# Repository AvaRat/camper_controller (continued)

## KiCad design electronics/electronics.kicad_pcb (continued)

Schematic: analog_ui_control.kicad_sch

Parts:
C16, C26: C_Polarized; CP_Radial_D5.0mm_P2.50mm
C25: 10uF; C_0805_2012Metric
C27: 100nF; C_0805_2012Metric
J3: Conn_01x08; TerminalBlock_Xinya_XY308-2.54-8P_1x08_P2.54mm_Horizontal

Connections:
+5V: C16.1, C25.2, C26.1, C27.2, J3.1; also elsewhere on the board
/central_control_unit/analog_ui_rmt_led: J3.3; also elsewhere on the board
/central_control_unit/btn_1: J3.4; also elsewhere on the board
/central_control_unit/btn_2: J3.5; also elsewhere on the board
/central_control_unit/btn_3: J3.6; also elsewhere on the board
/central_control_unit/btn_4: J3.7; also elsewhere on the board
/central_control_unit/btn_5: J3.8; also elsewhere on the board
GND_LP: C16.2, C25.1, C26.2, C27.1, J3.2; also elsewhere on the board

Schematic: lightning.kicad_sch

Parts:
C1, C3: C_Polarized; CP_Radial_D5.0mm_P2.50mm; not fitted
C2, C4: C; C_0805_2012Metric; not fitted
F6: 5A; ATO_fuse_holder; LCSC_part C2935871
J1: leds_ch1; TerminalBlock_Xinya_XY308-2.54-3P_1x03_P2.54mm_Horizontal
J20: leds_ch2; TerminalBlock_Xinya_XY308-2.54-3P_1x03_P2.54mm_Horizontal
J26: leds_ch3; TerminalBlock_Xinya_XY308-2.54-3P_1x03_P2.54mm_Horizontal
J27: leds_ch4; TerminalBlock_Xinya_XY308-2.54-3P_1x03_P2.54mm_Horizontal
Q6: Q_NMOS_GDS; SOT-23; Mrf_part AO3400-HXY; JLC C4748804
R1: 47k; R_0805_2012Metric
R2: 470R; R_0805_2012Metric
U2: ISO6740; SOIC-16W_7.5x10.3mm_P1.27mm; not fitted
U4: generic_dcdc; not fitted

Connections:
+5V_LEDs: C3.1, C4.1, J1.3, J20.3, J26.3, J27.3, U4.3 (VOUT)
+12V_HP: F6.1; also elsewhere on the board
/central_control_unit/LED_CH1: J1.2, U2.3 (INA), U2.14 (OUTA); also elsewhere on the board
/central_control_unit/LED_CH2: J20.2, U2.4 (INB), U2.13 (OUTB); also elsewhere on the board
/central_control_unit/LED_CH3: J26.2, U2.5 (INC), U2.12 (OUTC); also elsewhere on the board
/central_control_unit/LED_CH4: J27.2, U2.6 (IND), U2.11 (OUTD); also elsewhere on the board
/central_control_unit/led_en: R2.1; also elsewhere on the board
GND_HP: C1.2, C2.2, Q6.3 (S), R1.2, U2.9 (GND2), U2.15 (GND2); also elsewhere on the board
GND_LEDs: C3.2, C4.2, J1.1, J20.1, J26.1, J27.1, U4.4 (GND)
unnamed: Q6.2 (D), U4.2 (GND)
unnamed: Q6.1 (G), R1.1, R2.2
unnamed: U2.2 (GND1), U2.8 (GND1)
unnamed: C1.1, C2.1, F6.2, U4.1 (VIN)

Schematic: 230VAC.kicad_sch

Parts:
C9: 4.7uF; C_0805_2012Metric
C34: C; C_Disc_D3.0mm_W2.0mm_P2.50mm
D2: 1N4148W; D_SOD-123; MFG part nr 1N4148W; lcsc C917030
J21, J22: Conn_01x02; TerminalBlock_Xinya_XY308-2.54-2P_1x02_P2.54mm_Horizontal
Q5: Q_NMOS_GDS; SOT-23; Mrf_part AO3400-HXY; JLC C4748804
R22: 470R; R_0805_2012Metric
R23, R24: 100k; R_Axial_DIN0207_L6.3mm_D2.5mm_P7.62mm_Horizontal
R25: 4.7kΩ; R_0805_2012Metric
R41: 47k; R_0805_2012Metric
RL1: AZSR131-1AE-12D; PRE29-same-sky; MFG Part Nr PRE29-5V-S-450; not fitted
U17: LTV-814; DIP-4_W7.62mm; mouser 859-LTV-814S-TA1-A

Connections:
+3.3V: R25.1; also elsewhere on the board
+5V: D2.1 (K), RL1.2; also elsewhere on the board
/central_control_unit/230VAC/N_230VAC: J21.2, R24.1
/central_control_unit/230VAC/P_230VAC: J21.1, R23.1
/central_control_unit/ac_detect: C9.1, R25.2, U17.4; also elsewhere on the board
/central_control_unit/relay_out: R22.1; also elsewhere on the board
GND_LP: C9.2, Q5.3 (S), R41.2, U17.3; also elsewhere on the board
unnamed: C34.1, R23.2, U17.1
unnamed: C34.2, R24.2, U17.2
unnamed: D2.2 (A), Q5.2 (D), RL1.1
unnamed: J22.1, RL1.4
unnamed: J22.2, RL1.3
unnamed: Q5.1 (G), R22.2, R41.1

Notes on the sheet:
230VAC Detection
25mA LED current

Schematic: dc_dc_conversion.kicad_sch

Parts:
D1, D13, D14: LED; LED_1206_3216Metric
D15: D_Schottky; D_SMA
FB1: FerriteBead 47 Ohm; L_Walsin_WLFM201609x
J25: header; PinHeader_1x02_P2.54mm_Vertical
Q1: Q_NMOS_DGS; SOT-323_SC-70
Q2: Q_PMOS_DGS; SOT-323_SC-70
R3, R4, R18, R33, R34, R35: 4k7; R_0805_2012Metric
R36: 470R; R_0805_2012Metric
R37, R38: 47k; R_0805_2012Metric
U1: TLV1117-33; SOT-223-3_TabPin2; JLC C37359
U18: mini360; not fitted

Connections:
+3.3V: R4.2, U1.2 (VO); also elsewhere on the board
+5V: J25.2, R18.2, U1.3 (VI), U18.3 (VOUT); also elsewhere on the board
+12V: Q2.3 (S), R33.2, R38.1, U18.1 (VIN); also elsewhere on the board
/central_control_unit/USB_VIN: D15.2 (A), R36.2; also elsewhere on the board
/central_control_unit/dc_dc_conversion/USB_VBUS: D15.1 (K), J25.1
/central_control_unit/dc_dc_conversion/vin: Q2.1 (D)
GND_HP: FB1.2, U18.2 (GND), U18.4 (GND); also elsewhere on the board
GND_LP: D1.1 (K), D13.1 (K), D14.1 (K), FB1.1, Q1.3 (S), R37.2, U1.1 (GND); also elsewhere on the board
unnamed: D1.2 (A), R35.1
unnamed: D13.2 (A), R4.1
unnamed: D14.2 (A), R3.1
unnamed: Q1.1 (D), Q2.2 (G), R38.2
unnamed: Q1.2 (G), R36.1, R37.1
unnamed: R3.2, R18.1
unnamed: R33.1, R34.1
unnamed: R34.2, R35.2

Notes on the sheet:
USB_VSYS disconnets 12V to 5V DC/DC converter
Green LEDs
5V 6A max

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
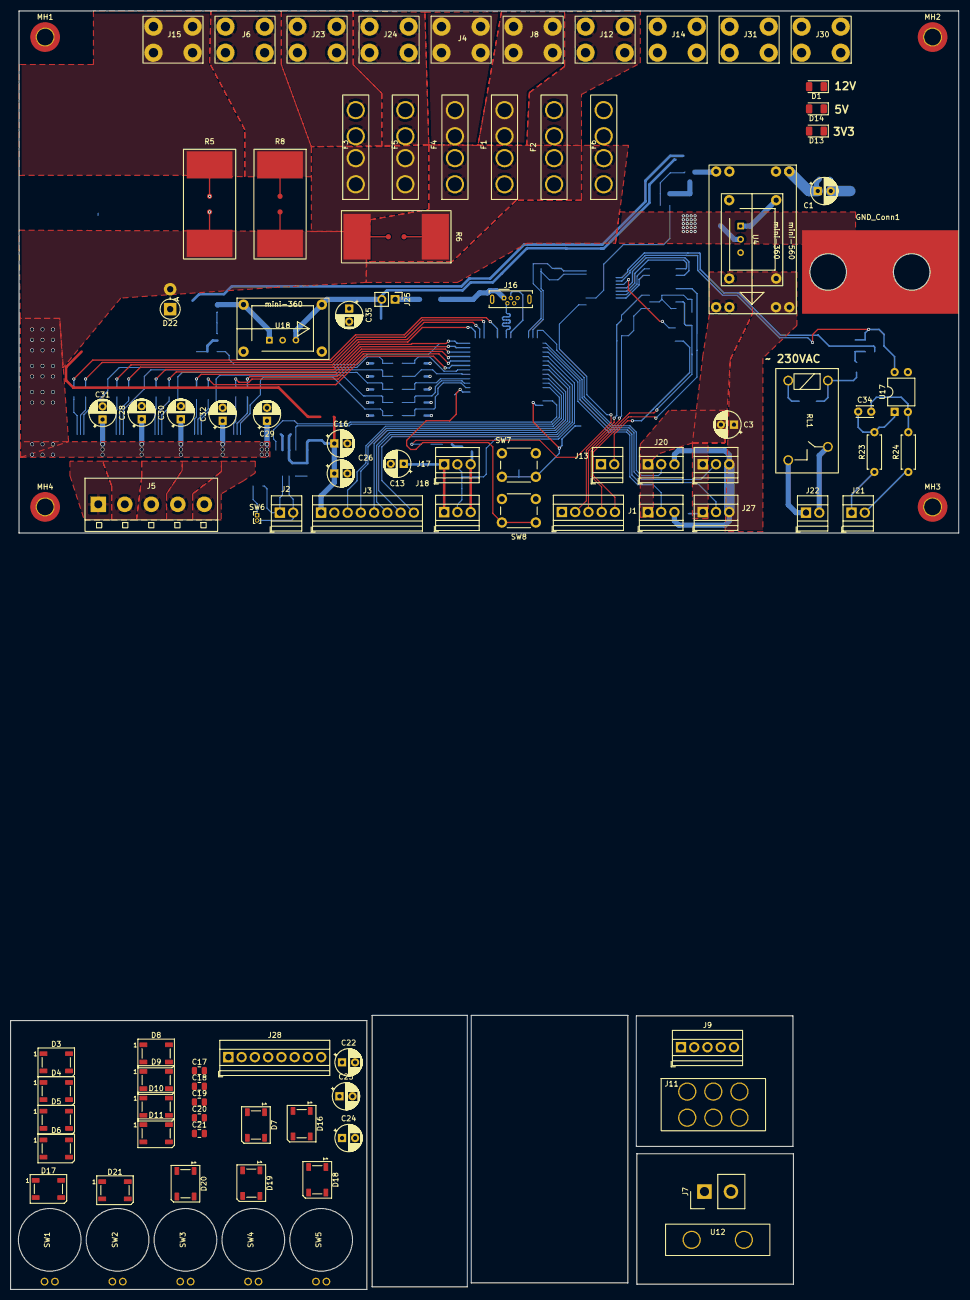
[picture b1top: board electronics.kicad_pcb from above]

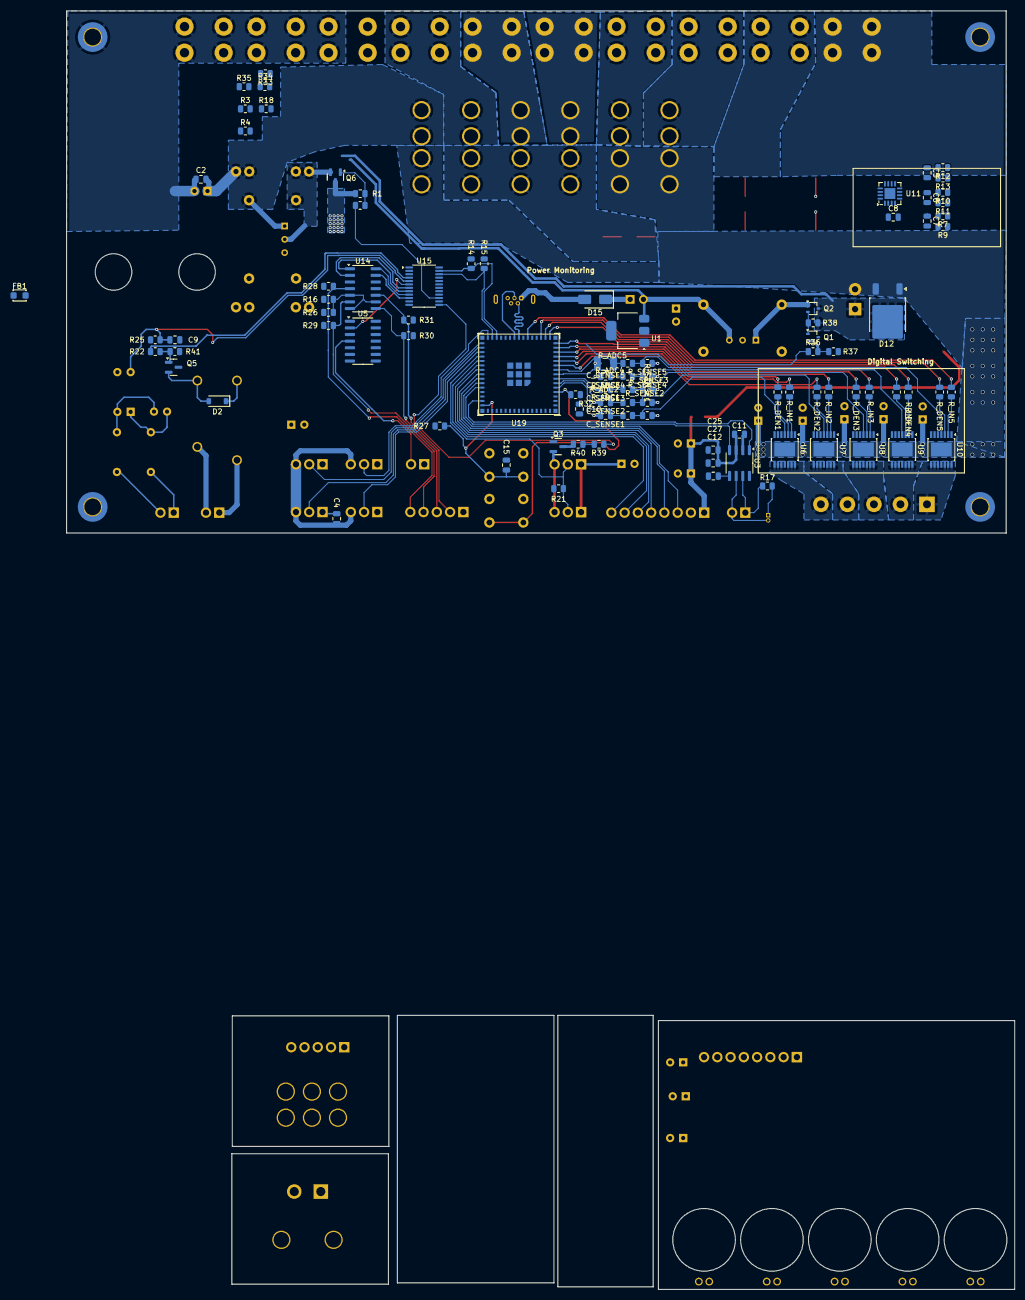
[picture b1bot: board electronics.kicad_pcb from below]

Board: 2 copper layers, 180.0 x 100.0 mm, 190 parts (93 on the bottom side), 154 nets.

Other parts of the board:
C35: C_Polarized; CP_Radial_D5.0mm_P2.50mm

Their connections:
+5V: C35.1; also elsewhere on the board
GND_HP: C35.2; also elsewhere on the board

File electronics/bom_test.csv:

"Reference","Value","Datasheet","Footprint","Qty","DNP","lcsc_part","TME"
"C1,C3,C13,C16,C22,C23,C24,C26,C28,C29,C30,C31,C32,C33","C_Polarized","~","Capacitor_THT:CP_Radial_D5.0mm_P2.50mm","14","","",""
"C2,C4,C14","C","~","Capacitor_SMD:C_0805_2012Metric","3","","",""
"C5,C6,C7,C8,C15","1uF","~","Capacitor_SMD:C_0805_2012Metric","5","","",""
"C9","4.7uF","~","Capacitor_SMD:C_0805_2012Metric","1","","",""
"C10","22uF","~","Capacitor_SMD:C_0805_2012Metric","1","","",""
"C11,C12,C27","100nF","~","Capacitor_SMD:C_0805_2012Metric","3","","",""
"C17,C18,C19,C20,C21,C25","10uF","~","Capacitor_SMD:C_0805_2012Metric","6","","",""
"D1,D13,D14","LED","~","LED_SMD:LED_1206_3216Metric","3","","",""
"D2","1N4148W","https://www.vishay.com/docs/85748/1n4148w.pdf","Diode_SMD:D_SOD-123","1","","",""
"D3,D4,D5,D6,D7,D8,D9,D10,D11,D16,D17,D18,D19,D20,D21","WS2812B","https://cdn-shop.adafruit.com/datasheets/WS2812B.pdf","LED_SMD:LED_WS2812B_PLCC4_5.0x5.0mm_P3.2mm","15","","",""
"D12","D_Schottky_AKA","https://www.vishay.com/docs/98173/v6pwl45.pdf","Package_TO_SOT_SMD:TO-252-2","1","","",""
"D15","D_Schottky","~","Diode_SMD:D_SMA","1","","",""
"D22","D_Schottky","~","Diode_THT:D_DO-15_P3.81mm_Vertical_AnodeUp","1","DNP","",""
"F1,F2,F3,F4,F5","20A","-- mixed values --","HeavyDuty:ATO_fuse_holder","5","","-- mixed values --",""
"F6","5A","~","HeavyDuty:ATO_fuse_holder","1","","",""
"FB1","FerriteBead 47 Ohm","~","Inductor_SMD:L_Walsin_WLFM201609x","1","","",""
"GND_Conn1,J11,U4,U12,U16,U18","~","","-- mixed values --","6","","",""
"J1","leds_ch1","~","TerminalBlock:TerminalBlock_Xinya_XY308-2.54-3P_1x03_P2.54mm_Horizontal","1","","",""
"J2","CAN","~","TerminalBlock:TerminalBlock_Xinya_XY308-2.54-2P_1x02_P2.54mm_Horizontal","1","","",""
"J3,J28","Conn_01x08","~","TerminalBlock:TerminalBlock_Xinya_XY308-2.54-8P_1x08_P2.54mm_Horizontal","2","","",""
"J4,J8,J12,J23,J24","Conn_01x01","~","HeavyDuty:keystone_m3_screw_terminal_vertical","5","","",""
"J5","DB12","https://www.lcsc.com/datasheet/lcsc_datasheet_2301061509_DOR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","HeavyDuty:5p_terminal_DB12","1","","",""
"J6","Inverter_Conn","~","HeavyDuty:keystone_m3_screw_terminal_vertical","1","","",""
"J7","grey_water_conn","~","Connector_Samtec_HPM_THT:Samtec_HPM-02-01-x-S_Straight_1x02_Pitch5.08mm","1","","",""
"J9,J10","water_sensor_conn","~","TerminalBlock:TerminalBlock_Xinya_XY308-2.54-5P_1x05_P2.54mm_Horizontal","2","","",""
"J13,J21,J22","Conn_01x02","~","TerminalBlock:TerminalBlock_Xinya_XY308-2.54-2P_1x02_P2.54mm_Horizontal","3","","",""
"J14,J25,J29,J30,J31","Conn_GND","~","HeavyDuty:keystone_m3_screw_terminal_vertical","5","","",""
"J15","Battery_Conn","~","HeavyDuty:keystone_m3_screw_terminal_vertical","1","","",""
"J16","USB_C_Receptacle_USB2.0_16P","https://www.usb.org/sites/default/files/documents/usb_type-c.zip","Connector_USB:USB_C_Receptacle_JAE_DX07S016JA1R1500","1","","",""
"J17,J18","Conn_01x03","~","TerminalBlock:TerminalBlock_Xinya_XY308-2.54-3P_1x03_P2.54mm_Horizontal","2","","",""
"J19","Conn_01x03","~","TerminalBlock:TerminalBlock_Xinya_XY308-2.54-3P_1x03_P2.54mm_Horizontal","1","DNP","",""
"J20","leds_ch2","~","TerminalBlock:TerminalBlock_Xinya_XY308-2.54-3P_1x03_P2.54mm_Horizontal","1","","",""
"J26","leds_ch3","~","TerminalBlock:TerminalBlock_Xinya_XY308-2.54-3P_1x03_P2.54mm_Horizontal","1","","",""
"J27","leds_ch4","~","TerminalBlock:TerminalBlock_Xinya_XY308-2.54-3P_1x03_P2.54mm_Horizontal","1","","",""
"Q1","Q_NMOS_DGS","~","Package_TO_SOT_SMD:SOT-323_SC-70","1","","",""
"Q2,Q3","Q_PMOS_DGS","~","Package_TO_SOT_SMD:SOT-323_SC-70","2","","",""
"Q4","Q_NMOS_GDS","https://wmsc.lcsc.com/wmsc/upload/file/pdf/v2/lcsc/231027181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","Package_TO_SOT_SMD:TO-252-2","1","","",""
"R1,R27,R32,R37,R38,R39","10k","~","Resistor_SMD:R_0805_2012Metric","6","","",""
"R2,R36","100R","~","Resistor_SMD:R_0805_2012Metric","2","","",""
"R3,R4,R18,R19,R20,R33,R34,R35","4k7","~","Resistor_SMD:R_0805_2012Metric","8","","",""
"R5,R8","0.001 Ohm 10W","https://www.mouser.pl/datasheet/2/392/Susumu_7_1_2024_MSRSF-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","HeavyDuty:MSRSF_shunt_resistor","2","","",""
"R6","0.003 Ohm 10W","https://www.mouser.pl/ProductDetail/Susumu/MSRSF5930P-3L00-F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","HeavyDuty:MSRSF_shunt_resistor","1","","",""
"R7,R9,R10,R11,R12,R13","10 ohm","-- mixed values --","Resistor_SMD:R_0805_2012Metric","6","","",""
"R14,R15,R21,R_DEN1,R_DEN2,R_DEN3,R_DEN4,R_DEN5,R_IN1,R_IN2,R_IN3,R_IN4,R_IN5","4.7k","-- mixed values --","Resistor_SMD:R_0805_2012Metric","13","","",""
"R16,R23,R24,R26","100k","-- mixed values --","-- mixed values --","4","","",""
"R17","120","~","Resistor_SMD:R_0805_2012Metric","1","","",""
"R22","50 Ohm","~","Resistor_SMD:R_0805_2012Metric","1","","",""
"R25","4.7kΩ","~","Resistor_SMD:R_0805_2012Metric","1","","",""
"R28,R29,R30,R31","1M","~","Resistor_SMD:R_0805_2012Metric","4","","",""
"RL1","AZSR131-1AE-12D","https://www.mouser.pl/datasheet/2/1628/pre29-3510988.pdf","HeavyDuty:PRE29-same-sky","1","","",""
"SW1,SW2,SW3,SW4,SW5","SW_Push","~","analog_ui:button_12mm","5","","",""
"SW6","SW_DIP_x01","~","Connector_PinHeader_1.00mm:PinHeader_1x02_P1.00mm_Vertical","1","","",""
"SW7","RST_BTN","~","Button_Switch_THT:SW_PUSH_6mm_H4.3mm","1","","",""
"SW8","FLASH_BTN","~","Button_Switch_THT:SW_PUSH_6mm_H4.3mm","1","","",""
"U1","TLV1117-33","http://www.ti.com/lit/ds/symlink/tlv1117.pdf","Package_TO_SOT_SMD:SOT-223-3_TabPin2","1","","",""
"U3","TJA1051T-3","http://www.nxp.com/docs/en/data-sheet/TJA1051.pdf","Package_SO:SOIC-8_3.9x4.9mm_P1.27mm","1","","",""
"U5,U14","LM339_4ch","","Package_SO:SOIC-14_3.9x8.7mm_P1.27mm","2","","",""
"U6,U7,U8,U9,U10","BTS7006","https://www.infineon.com/dgdl/Infineon-BTS7004-1EPP-DS-v01_0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","Package_SO:Infineon_PG-TSDSO-14-22","5","","",""
"U11","INA3221","http://www.ti.com/lit/ds/symlink/ina3221.pdf","Package_DFN_QFN:Texas_RGV0016A_VQFN-16-1EP_4x4mm_P0.65mm_EP2.1x2.1mm","1","","",""
"U13","CNY17-1","http://www.vishay.com/docs/83606/cny17.pdf","Package_TO_SOT_SMD:SOT-23-6","1","","",""
"U15","TCA9555PWR","http://www.ti.com/lit/ds/symlink/tca9555.pdf","Package_SO:TSSOP-24_4.4x7.8mm_P0.65mm","1","","","TCA9554APWR"
"U17","H11AA1","https://www.vishay.com/docs/83608/h11aa1.pdf","Package_DIP:DIP-6_W7.62mm","1","","",""
"U19","ESP32-S3-MINI-1","https://www.espressif.com/sites/default/files/documentation/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","PCM_Espressif:ESP32-S3-MINI-1U","1","","",""

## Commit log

2024-09-15 add gitignore
2024-09-15 initial basic structure with BTS driver
2024-09-23 minor progress
2024-09-23 from legion
2024-10-21 add lvgl pv sim
2024-11-17 gitignore update
2024-11-17 bulk update. UI working nice on 7inch screen under Linux (RPI) framebuffer
2024-11-17 main app on top lvl
2024-11-17 add lv_conf and cross compile commands
2024-11-24 ina first try with rp pico. both, read and write works fine though. some functions not
2024-12-08 esp-crow-panel-7 works
2024-12-14 small_3 dynamic png display from sd card works
2024-12-15 much cleaner files structure. more observers and ESP-specific stuff separation
2024-12-20 progress made on electronics part
2025-01-01 hss GPIO implemented, compiling fine
2025-01-14 big-55A-switch added
2025-01-18 compiling and linking fine. start to make bigger program based on components
2025-01-19 hss_test_thread and DC/DC converter blowup after short-circuit test
2025-01-20 porady od MichalaG
2025-01-21 LED RGB and temp sensor added
2025-01-23 lisbon flight changes
2025-01-29 flight back. different layout. start analog ui
2025-01-31 no tracks, but placement looks good
2025-02-03 add some lcsc and TME part numbers
2025-02-03 add some more part nummbers
2025-02-03 nerd weekend update
2025-02-08 added analog_ui based on led_strip. flashin, timers, colors and brightness works. all in c++ sty;e
2025-02-09 basic temp sensor on RMT DS18B20. analogUI stopped working...
2025-02-14 from dell
2025-02-16 start to do proper layout
2025-02-19 capacitors added. universal dc/dc converters
2025-02-19 small progress on routing
2025-02-20 very simple io_expander class
2025-02-20 refactor ws component
2025-02-24 project cleanup
2025-02-24 project descriptions added
2025-02-24 Rename design_decision.md to design_decisions.md
2025-02-24 readme refinement
2025-02-25 start to create BOM and finalising symbol fields
2025-02-26 progres on layouting
2025-03-02 layouting progress. some 3d models upload
